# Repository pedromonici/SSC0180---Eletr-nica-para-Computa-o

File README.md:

# Projeto#1: Fonte de Tensão

## DESCRIÇÃO:
Projeto de uma Fonte de Tensão entre 3V a 12V com capacidade de 100mA

## Diagrama da Fonte

**NOTA: A resistência de 30 ohms que pode ser vista no circuito é apenas uma forma de representar a presença do regulador de tensão LM 317. A única função dessa resistência é causar uma queda de tensão similar a do LM 317 que permite a simulação no falstad**
### Link para o circuito
http://tinyurl.com/yc745h6d

### Explicação dos valores escolhidos:
- Capacitor:
  
  A partir da equação para cálculo da tensão:

  Assumindo  e sabendo que , temos:

  Dessa forma, um Capacitor de  é suficiente para a fonte do projeto.

- Circuito Regulador de Tensão:
  
  A partir da datasheet da "Texas Instruments"(https://tinyurl.com/y7voskoq), obtêm-se a fórmula:

  Onde:
	-  é a tensão de saída.
	-  é um resistor.
	-  é o potênciometro.
	-  é a resistência em série do potênciômetro.
  
  Assim, para obter  na saída com o potênciometro em seu valor mínimo e  com o potênciometro em seu valor máximo, os seguintes valores são necessários para satisfazer a equação:
  
  Para , o potêncimetro deve estar em um valor próximo de  e . Logo, .

  E para , utilizando , .
	
### Video da simulação do projeto
https://youtu.be/dQlkS4CVClo

### Componentes:
* Diodo (x6) - R$ 0,66
* Transformador 110v para 24v - R$ 29,90
* Capacitor 100μF - R$ 0,10
* Capacitor 10μF (x3) - R$ 0,42
* Capacitor de 8mF (1mF x 8) - R$ 3,84
* Potenciômetro 5kΩ - R$ 1,09
* Resistor 110Ω - R$ 0,12
* Resistor 1kΩ - R$ 0,08
* LM 317 - R$ 2,75
* Fusível - R$ 0,42
* **TOTAL: R$ 39,38**

## Esquemático do circuito no EAGLE

## PCB do circuito no EAGLE

## Participantes:
* **Gabriel da Cunha Dertoni(11795717)** - [GabrielDertoni](https://github.com/GabrielDertoni)

* **Eduardo Henrique Porto Silva(11796656)**  - [EduardoPortoSilva](https://github.com/EduardoPortoSilva)

* **Pedro Henrique Borges Monici(10816732)** - [pedromonici](https://github.com/pedromonici)

* **Tulio Santana Ramos(11795526)** - [Tulip-bcc](https://github.com/Tulip-bcc)

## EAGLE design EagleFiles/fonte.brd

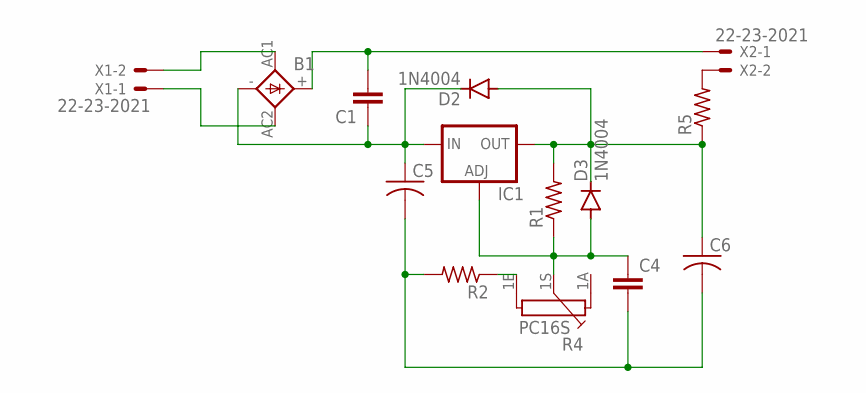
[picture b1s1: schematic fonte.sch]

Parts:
B1: 2KBB-R
C1: C2,5-3; C2.5-3
C4: C2.5/2; C2.5-2
C5, C6: C-US025-024X044; C025-024X044
D2, D3: 1N4004; DO41-10
IC1: LM317L; 317L
R1, R2, R5: R-US_0204/7; 0204/7
R4: PC16S
X1, X2: 22-23-2021

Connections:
unnamed: B1.AC2, X1.1
unnamed: B1.AC1, X1.2
unnamed: B1.+, C1.2, X2.1
unnamed: B1.-, C1.1, C5.1, D2.C, IC1.3 (IN)
unnamed: C4.2, C5.2, C6.2, R2.2
unnamed: C6.1, D2.A, D3.C, IC1.2 (OUT), R1.2, R5.1
unnamed: C4.1, D3.A, IC1.1 (ADJ), R1.1, R4.1S
unnamed: R2.1, R4.1E
unnamed: R5.2, X2.2

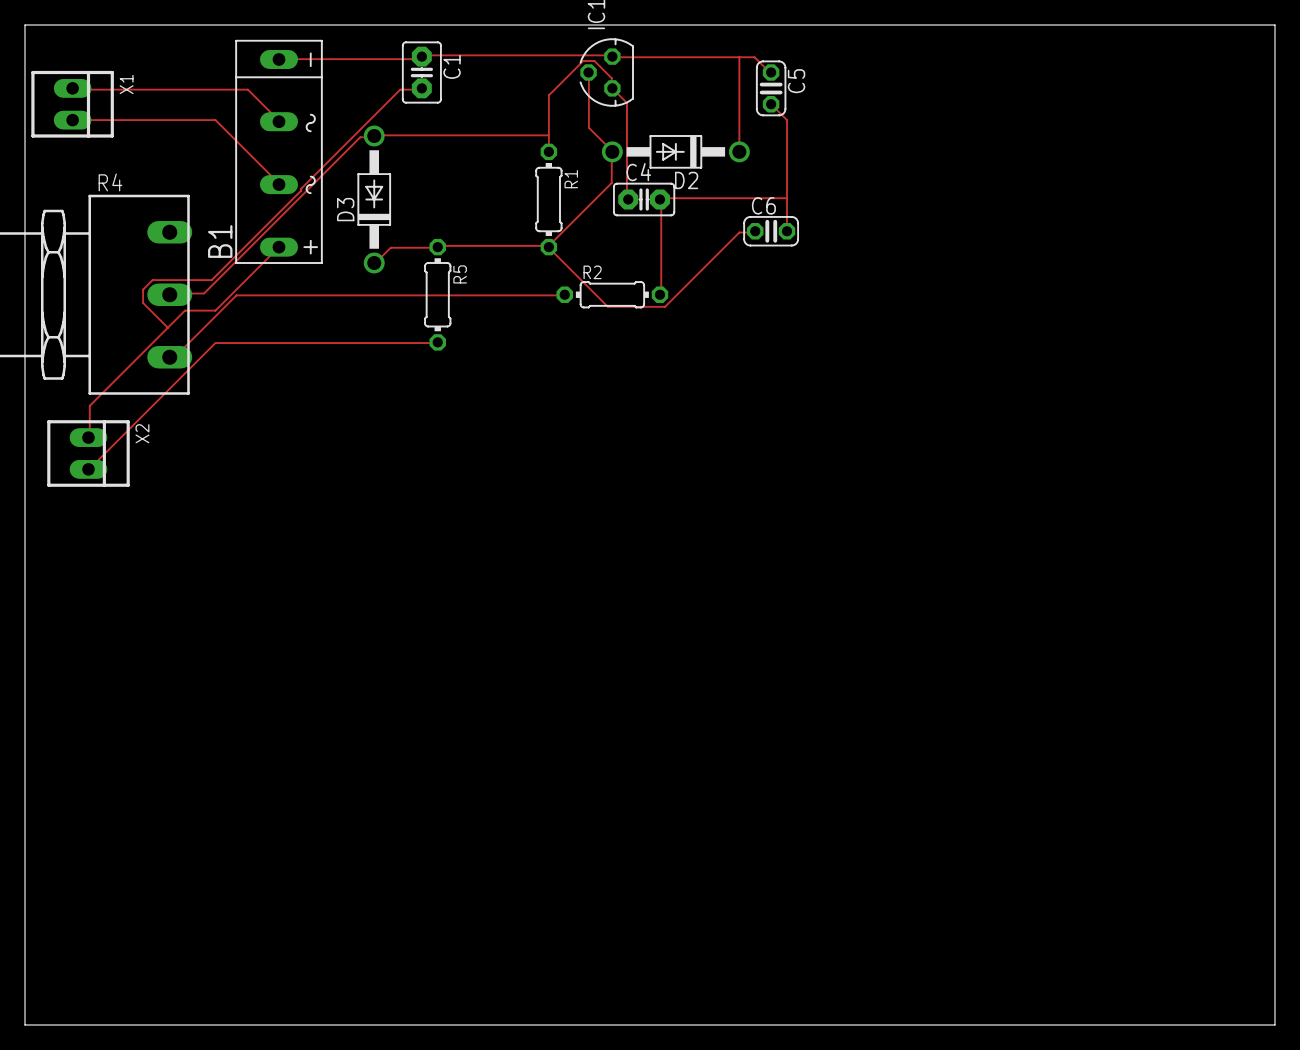
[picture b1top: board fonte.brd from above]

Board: 2 copper layers, 100.0 x 80.0 mm, 14 parts (0 on the bottom side), 9 nets.

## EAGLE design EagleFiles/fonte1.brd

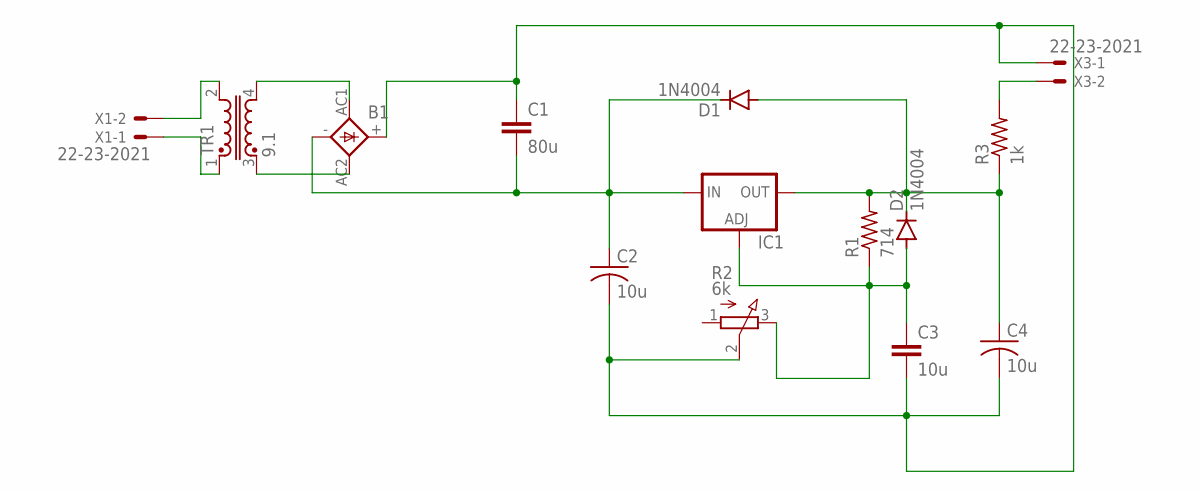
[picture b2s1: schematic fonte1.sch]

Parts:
B1: 1KAB
C1: 80u; C025-025X050
C2, C4: 10u; C025-024X044
C3: 10u; C025-025X050
D1, D2: 1N4004; DO41-10
IC1: LM317TL; 317TL
R1: 714; 0204/7
R2: 6k; 3RP/1610N
R3: 1k; 0204/7
TR1: 9.1; U15
X1, X3: 22-23-2021

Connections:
unnamed: TR1.2, X1.2
unnamed: TR1.1, X1.1
unnamed: B1.AC1, TR1.4
unnamed: B1.AC2, TR1.3
unnamed: B1.-, C1.2, C2.1, D1.C, IC1.3 (IN)
unnamed: R3.2, X3.2
unnamed: C4.1, D1.A, D2.C, IC1.2 (OUT), R1.2, R3.1
unnamed: C3.1, D2.A, IC1.1 (ADJ), R1.1, R2.3 (E)
unnamed: B1.+, C1.1, C2.2, C3.2, C4.2, R2.2 (S), X3.1

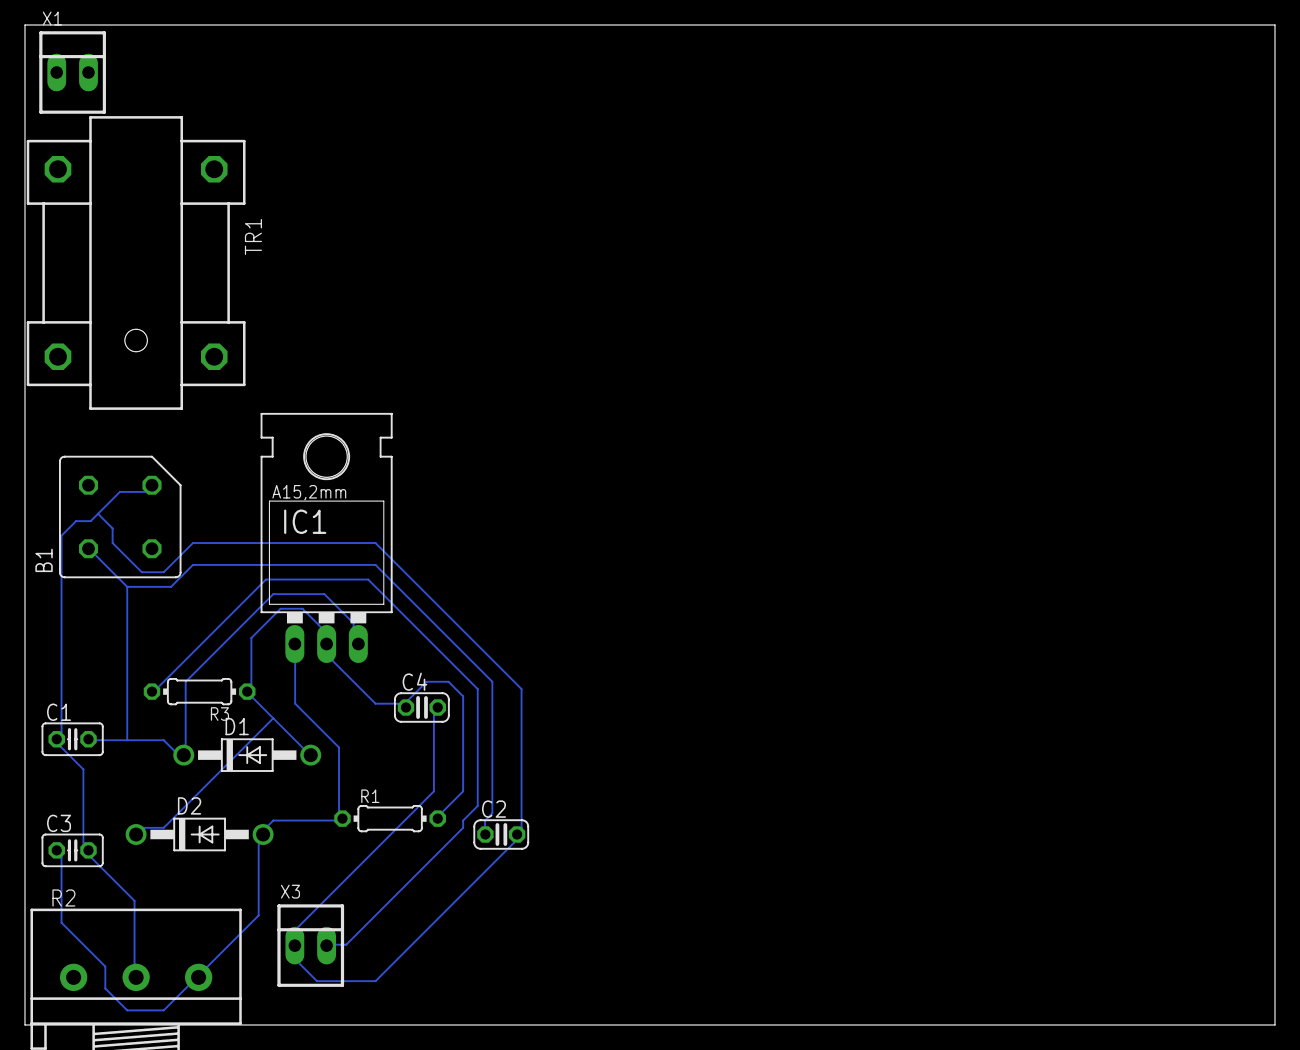
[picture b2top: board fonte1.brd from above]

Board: 2 copper layers, 100.0 x 80.0 mm, 14 parts (0 on the bottom side), 9 nets.

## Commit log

2020-06-13 Circuito
2020-06-13 Capacitor
2020-06-13 Formulas
2020-06-15 Adicionados os preços dos componentes
2020-06-15 Readme
2020-06-15 Total está uma linha a baixo
2020-06-15 Alterações de valores
2020-06-15 Atualizado o preço total
2020-06-15 Add files via upload
    new image
2020-06-30 Corrigir circuito
2020-06-30 Postando arquivos do EAGLE
